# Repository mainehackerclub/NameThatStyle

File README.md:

NameThatStyle
=============

For Name that Style Discovery Museum exhibit.

How to upload the program using Arduino IDE
===========================================
1. Add the following to the \arduino\hardware\arduino\boards.txt file (works for Arduino 1.0)

  ##############################################################

  atmega328smd16e.name=ATmega328 SMD (16Mhz Ext, no boot)

  atmega328smd16e.upload.protocol=stk500
  atmega328smd16e.upload.maximum_size=30720
  atmega328smd16e.upload.speed=57600

  atmega328smd16e.bootloader.low_fuses=0xFF
  atmega328smd16e.bootloader.high_fuses=0xDA
  atmega328smd16e.bootloader.extended_fuses=0x05
  atmega328smd16e.bootloader.path=arduino:atmega
  atmega328smd16e.bootloader.unlock_bits=0x3F
  atmega328smd16e.bootloader.lock_bits=0x0F

  atmega328smd16e.build.mcu=atmega328p
  atmega328smd16e.build.f_cpu=16000000L
  atmega328smd16e.build.core=arduino:arduino
  atmega328smd16e.build.variant=arduino:eightanaloginputs

  ##############################################################

  atmega328smd8i.name=ATmega328 SMD (8Mhz Int, no boot)

  atmega328smd8i.upload.protocol=stk500
  atmega328smd8i.upload.maximum_size=30720
  atmega328smd8i.upload.speed=57600

  atmega328smd8i.bootloader.low_fuses=0xE2
  atmega328smd8i.bootloader.high_fuses=0xD7
  atmega328smd8i.bootloader.extended_fuses=0x05
  atmega328smd8i.bootloader.unlock_bits=0x3F
  atmega328smd8i.bootloader.lock_bits=0x0F

  atmega328smd8i.build.mcu=atmega328p
  atmega328smd8i.build.f_cpu=8000000L
  atmega328smd8i.build.core=arduino:arduino
  atmega328smd8i.build.variant=arduino:eightanaloginputs

  ##############################################################

  atmega328smd1i.name=ATmega328 SMD (1Mhz Int, no boot)

  atmega328smd1i.upload.protocol=stk500
  atmega328smd1i.upload.maximum_size=30720
  atmega328smd1i.upload.speed=57600

  atmega328smd1i.bootloader.low_fuses=0x62
  atmega328smd1i.bootloader.high_fuses=0xD7
  atmega328smd1i.bootloader.extended_fuses=0x05
  atmega328smd1i.bootloader.unlock_bits=0x3F
  atmega328smd1i.bootloader.lock_bits=0x0F

  atmega328smd1i.build.mcu=atmega328p
  atmega328smd1i.build.f_cpu=1000000L
  atmega328smd1i.build.core=arduino:arduino
  atmega328smd1i.build.variant=arduino:eightanaloginputs

2. Restart Arduino IDE
3. Set the correct board Menu > Tools > Boards > ATmega328 SMD (8Mhz Int, no boot)
4. Select your programmer Menu > Tools > Programmer
5. Upload via Menu > File > Upload using programmer

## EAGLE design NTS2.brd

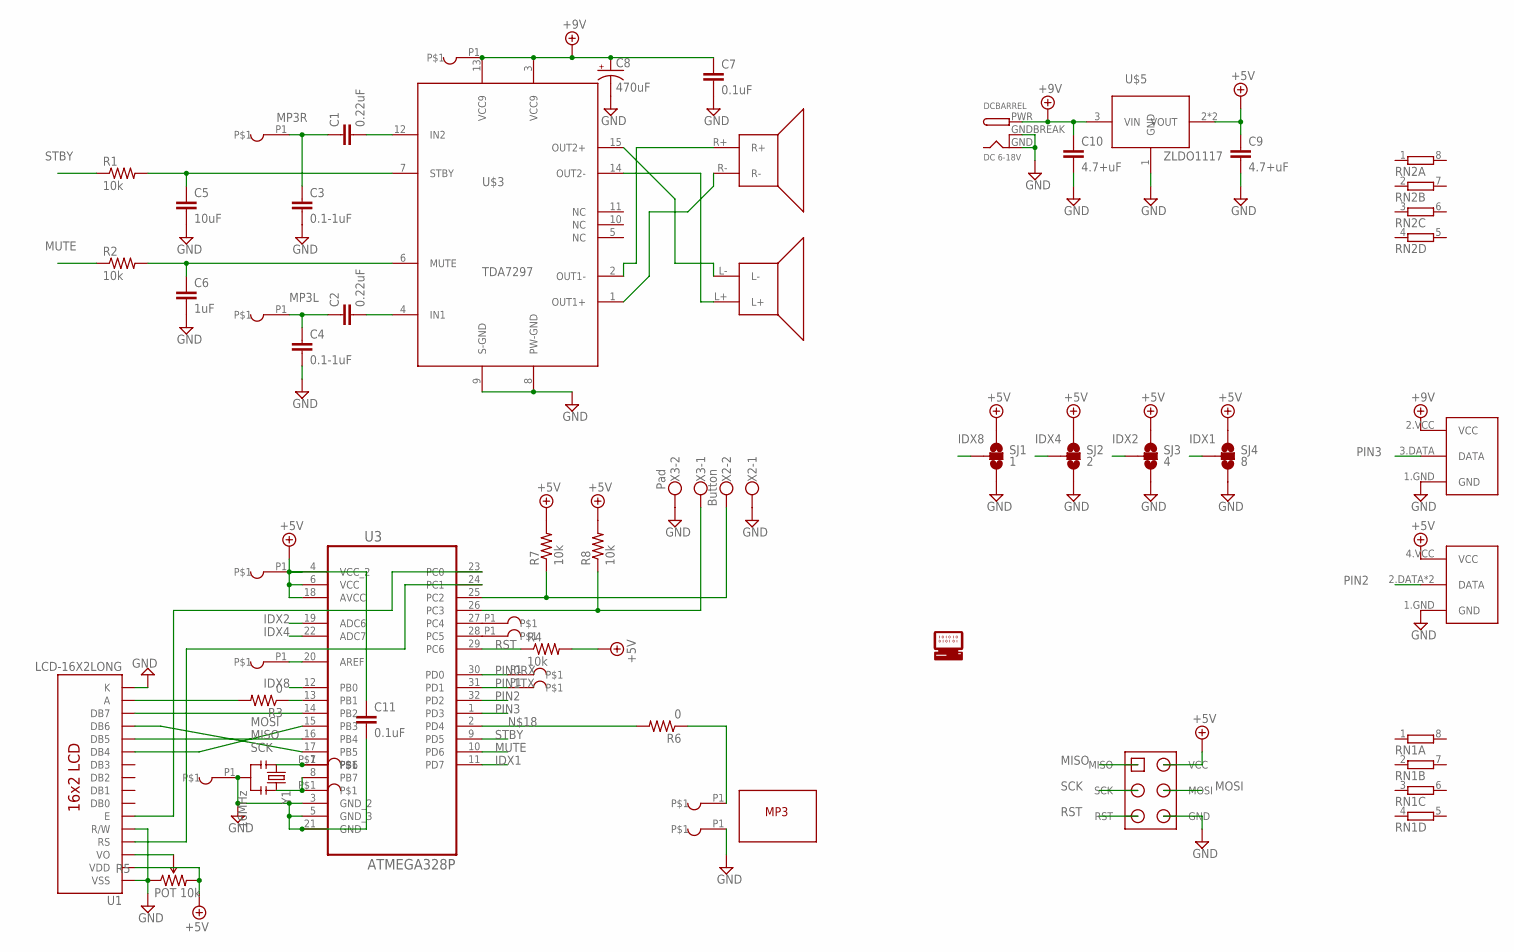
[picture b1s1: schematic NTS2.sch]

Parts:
AREF: AREF; JMP1
C1, C2: 0.22uF; 0805-XL
C3, C4: 0.1-1uF; 0805-XL
C5: 10uF; 0805-XL
C6: 1uF; 0805-XL
C7, C11: 0.1uF; 0805-XL
C8: 470uF; CAP-PTH-200-POL-HOR-R-600
C9: 4.7+uF; 1206
C10: 4.7+uF; 0805-XL
DCBARREL: DC 6-18V; DCJACK_2MM_PTH
GND: GND; JMP1
MP3+: M+; JMP1-RECT
MP3-: M-; JMP1-RECT
MP3-L: L; JMP1-RECT
MP3-R: R; JMP1-RECT
PB6: PB6; JMP1-SMD-100
PB7: PB7; JMP1-SMD-100
PC4: A4; JMP1
PC5: A5; JMP1
PD0: Rx; JMP1
PD1: Tx; JMP1
R1, R2, R4, R7, R8: 10k; 0805-XL
R3, R6: 0; 1206
R5: POT 10k; TRIM_POT_PTH
RN1: 4R-NCAT16; CAT16
RN2: 4R-N0402ARV341; 4X0402ARV341
SJ1: 1; SJ_2_BIN-PTH
SJ2: 2; SJ_2_BIN-PTH
SJ3: 4; SJ_2_BIN-PTH
SJ4: 8; SJ_2_BIN-PTH
U1: LCD-16X2LONG; LCD-16X2-LONG
U3: ATMEGA328P; QFP80P900X900X120-32N-LD
U$1: OUTLINE-MP3-MDM
U$2: HEAD-2X3-ISPISP6NLL; HEADER2X3-PTH-NOLABEL-LONG
U$3: TDA7297
U$4: SPEAKERSPTH; SPEAKER-5105
U$5: ZLDO1117; SOT223-3-L
U$6: RF-TRANSMITTER; RF-TRANSMIT
U$7: RF-RECEIVER
U$8: LOGO_HM512; LOGO_HM_512
VCC: VCC; JMP1
VIN: Vin; JMP1
X2: Button; CON-SCREW2
X3: Pad; CON-SCREW2
Y1: 16MHz; SMD-RESONATOR-320-130-PRQC

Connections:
+5V: C9.1, C11.1, R4.2, R5.3 (CW), R7.2, R8.2, SJ1.1, SJ2.1, SJ3.1, SJ4.1, U1.2 (VDD), U3.4 (VCC_2), U3.6 (VCC), U3.18 (AVCC), U$2.VCC, U$5.2 (VOUT), U$5.4 (VOUT), U$7.4.VCC (VCC), VCC.P1
+9V: C7.1, C8.2+ (+), C10.1, DCBARREL.PWR, U$3.3 (VCC9), U$3.13 (VCC9), U$5.3 (VIN), U$6.2.VCC (VCC), VIN.P1
AREF: AREF.P1, U3.20 (AREF)
GND: C3.2, C4.2, C5.2, C6.2, C7.2, C8.1- (-), C9.2, C10.2, C11.2, DCBARREL.GND, DCBARREL.GNDBREAK, GND.P1, MP3-.P1, R5.1 (CCW), SJ1.3, SJ2.3, SJ3.3, SJ4.3, U1.1 (VSS), U1.5 (R/W), U1.16 (K), U3.3 (GND_2), U3.5 (GND_3), U3.21 (GND), U$2.GND, U$3.8 (PW-GND), U$3.9 (S-GND), U$5.1 (GND), U$6.1.GND (GND), U$7.1.GND (GND), X2.1, X3.2, Y1.2.GND
IDX1: SJ4.2 (2.C), U3.11 (PD7)
IDX2: SJ3.2 (2.C), U3.19 (ADC6)
IDX4: SJ2.2 (2.C), U3.22 (ADC7)
IDX8: SJ1.2 (2.C), U3.12 (PB0)
MISO: U1.12 (DB5), U3.16 (PB4), U$2.MISO
MOSI: U1.11 (DB4), U3.15 (PB3), U$2.MOSI
MP3L: C2.1, C4.1, MP3-L.P1
MP3R: C1.1, C3.1, MP3-R.P1
MUTE: R2.1, U3.10 (PD6)
unnamed: U$3.15 (OUT2+), U$4.L-
unnamed: U$3.14 (OUT2-), U$4.L+
unnamed: U$3.2 (OUT1-), U$4.R+
unnamed: U$3.1 (OUT1+), U$4.R-
unnamed: R7.1, U3.25 (PC2), X2.2
unnamed: C1.2, U$3.12 (IN2)
unnamed: R8.1, U3.26 (PC3), X3.1
unnamed: C2.2, U$3.4 (IN1)
unnamed: C6.1, R2.2, U$3.6 (MUTE)
unnamed: C5.1, R1.2, U$3.7 (STBY)
unnamed: R3.1, U3.13 (PB1)
unnamed: U1.14 (DB7), U3.14 (PB2)
unnamed: PB6.P$1, U3.7 (PB6), Y1.1
unnamed: PB7.P$1, U3.8 (PB7), Y1.3
unnamed: R5.2 (WIPER), U1.3 (VO)
unnamed: U1.6 (E), U3.23 (PC0)
unnamed: U1.4 (RS), U3.24 (PC1)
unnamed: R6.2, U3.2 (PD4)
unnamed: R3.2, U1.15 (A)
unnamed: MP3+.P1, R6.1
unnamed: PC4.P1, U3.27 (PC4)
unnamed: PC5.P1, U3.28 (PC5)
PIN0RX: PD0.P1, U3.30 (PD0)
PIN1TX: PD1.P1, U3.31 (PD1)
PIN2: U3.32 (PD2), U$7.2.DATA (DATA), U$7.3.DATA (DATA)
PIN3: U3.1 (PD3), U$6.3.DATA (DATA)
RST: R4.1, U3.29 (PC6), U$2.RST
SCK: U1.13 (DB6), U3.17 (PB5), U$2.SCK
STBY: R1.1, U3.9 (PD5)

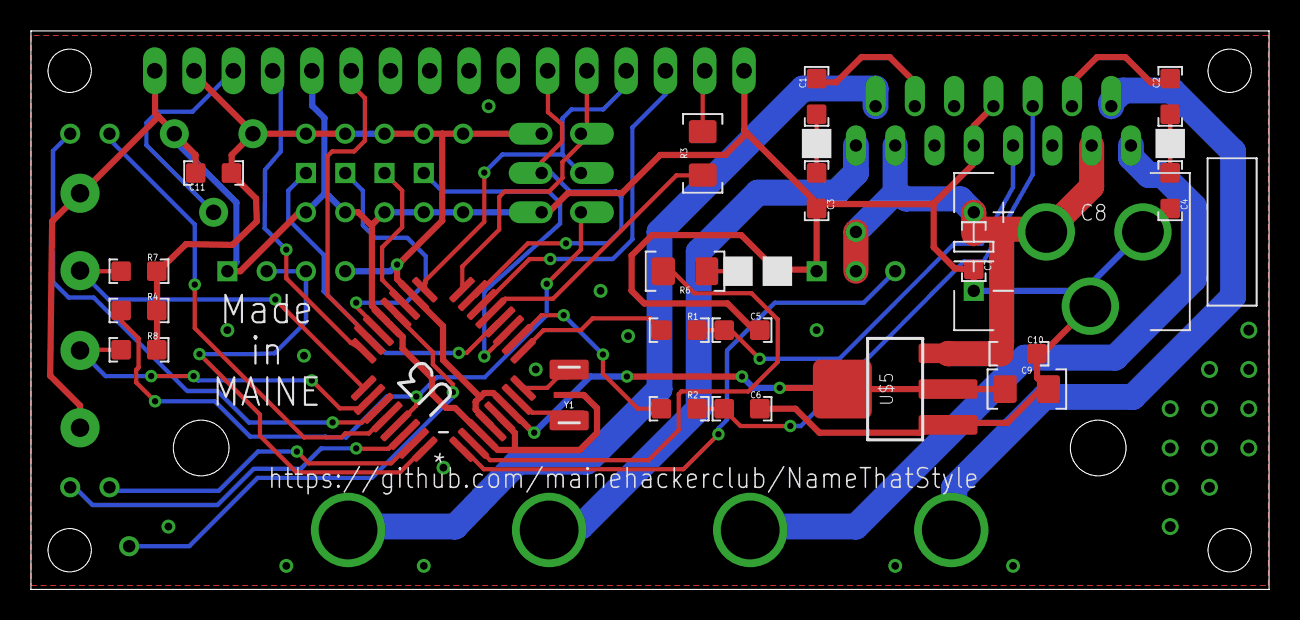
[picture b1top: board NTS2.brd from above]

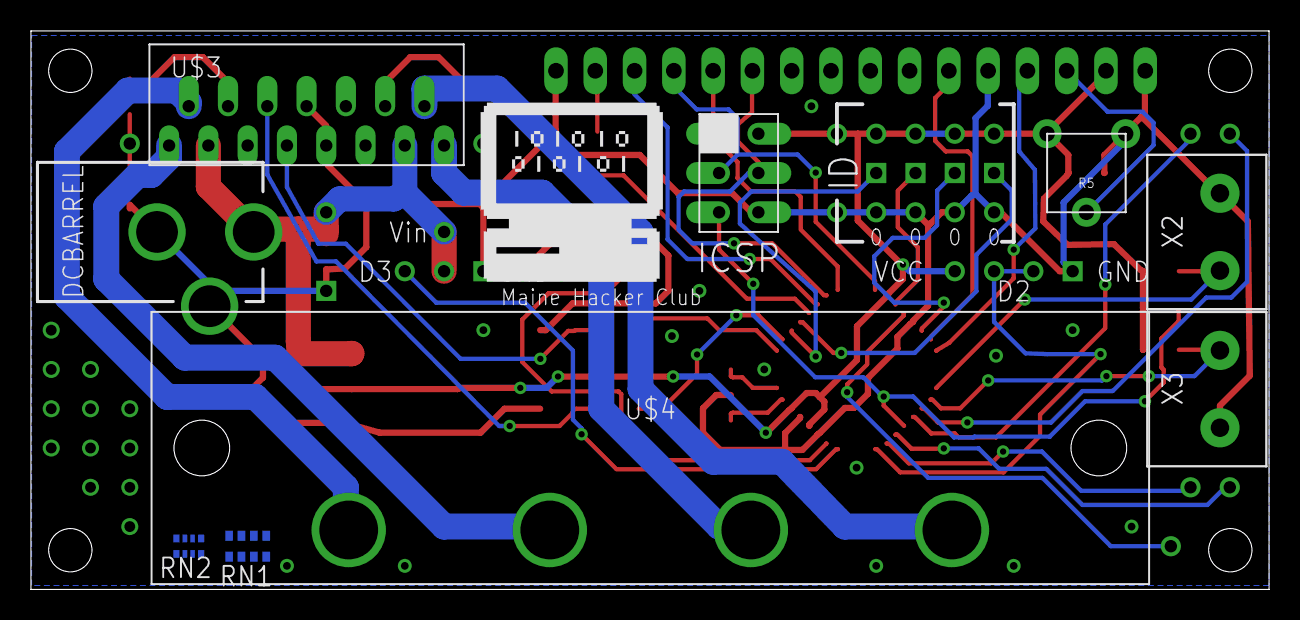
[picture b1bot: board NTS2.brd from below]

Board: 2 copper layers, 80.1 x 36.1 mm, 53 parts (16 on the bottom side), 42 nets.

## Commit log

2013-09-13 beta
2013-10-02 alfa
2013-10-09 clean up
2013-10-09 Test
2013-10-23 Added music tracks from cd's 3 & 4 were unreadable
2013-10-24 Fixes
